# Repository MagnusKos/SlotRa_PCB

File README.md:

# SlotRa_PCB
A rework of [fakeTec_pcb](https://github.com/gargomoma/fakeTec_pcb) project compatible with [Meshtastic](https://meshtastic.org/)®. Based on nRF52840 small boards and cheap LoRa modules identical to RA-62.
This rework rearranges the PCB to become a size of BL-5C battery. It's placed in a custom case project named SlotRa (_to be published_).

__This Readme.md is a modified version of the original one by gargomoma, Big Thanks to them.__

# Pictures
<details><summary>Click to open</summary>

| Just a PCB | A PCB with a batt | A PCB in a slot |
| :------------ | :------------ | :------------ |
| |  |  |

</details>

## Features
- i2c side ports ready to connect an OLED SSD1306 screen.
- Battery sensing: You can use SMD resistors or through-hole.
- 2mm mounting holes.
- Compatible with HT-RA62 / RA-01SH LoRa modules (and probably others with similar footprint).
- The variant & design is based on the DIY
<a href="https://github.com/mrekin/MeshtasticCustomBoards/tree/main/firmware/variants/diy/promicro_diy_m" target="_blank">ProMicro variant</a>.
- As MCU board its used <a href="https://github.com/joric/nrfmicro/wiki/Alternatives#supermini-nrf52840l" target="_blank">ProMicro/SuperMini</a>

# Variants

(aka firmware files)

| Version | Lora Modules | Official Repo link | Unofficial Repo link |
| :------------ | :---------------------------- | :-----------------| :-----------------|
| With TCXO | EByte E22/E220-xxxM-22S/HT-RA62 | <a href="https://github.com/meshtastic/firmware/tree/master/variants/diy/nrf52_promicro_diy_tcxo" target="_blank">Official repo - With TCXO</a> | <a href="https://github.com/mrekin/MeshtasticCustomBoards/tree/main/firmware/variants/diy/promicro_diy_m" target="_blank">With TCXO</a> @mrekin/MeshtasticCustomBoards|
| Without TCXO | EByte E22/E220-xxxMM-22S/RA-01SH | <a href="https://github.com/meshtastic/firmware/tree/master/variants/diy/nrf52_promicro_diy_xtal" target="_blank">Official repo - Without TCXO</a> | <a href="https://github.com/mrekin/MeshtasticCustomBoards/tree/main/firmware/variants/diy/promicro_diy_mm" target="_blank">Without TCXO</a> @mrekin/MeshtasticCustomBoards|

ℹ️If you don't want to build your own image use <a href="https://mrekin.duckdns.org/flasher/" target="_blank">mrekin's flasher</a>

# Bill of materials

| Part | Source | Cost&nbsp;(€) | Note |
| :------------ | :---------------------------- | :-----------------| :-----------------|
| ProMicro (aka NiceNano) | <a href="https://www.aliexpress.com/item/1005006446457448.html" target="_blank">AliExpress</a><br /> <a href="https://www.aliexpress.com/item/1005007738886550.html" target="_blank">AliExpress</a> | 5€ <br /> 2x for 5€ | |
| HT-RA62 | <a href="https://www.aliexpress.com/item/1005005543917617.html" target="_blank">AliExpress</a> | 5€ | You can also use <a href="https://www.aliexpress.com/item/1005002561194884.html">RA-01SH</a> |
| 2x Through Hole Resistors // SMD resistor | <a href="https://www.aliexpress.com/item/1005006044241818.html" target="_blank">AliExpress</a> | 3€ pack<br /> 0.1€/resistor | You can buy a package of multiple values for a few €.<br /> Choose depending on material you already have &/or soldering skills. I'm using 2x 1M ohms |
| OLED SSD1306 i2c (optional) | <a href="https://www.aliexpress.com/item/1005005970901119.html" target="_blank">AliExpress</a> | 1.5€ | No need to solder, just be careful and add some tape in between the boards to avoid a short. |
| Battery connection (optional) | <a href="https://www.aliexpress.com/item/1005002564191148.html" target="_blank">AliExpress</a> | 2€ pack<br /> 0.4€/unit | This is an example. |
| Antenna pigtail (recommended) | <a href="https://www.aliexpress.com/item/4001287491018.html" target="_blank">AliExpress</a> | 2€ | I saw that it underperformed with a cheap black pigtail, after using one of these, it worked fine. |
| PCB |  | 2€ pack of 5<br /> 0.4€/unit | Use your favourite company to get the PCB. |
| 2x Buttons | <a href="https://www.aliexpress.com/item/4001125532910.html" target="_blank">AliExpress</a> | 1.8€ pack<br /> 0.1€/button | You can buy a package of 100 for a few €.<br /> I couldn't find a part code, search for "3*4*2.0 2 Pin Button" |
| [#16](https://github.com/gargomoma/fakeTec_pcb/issues/16) lupusworax's v4<br /> Mosfets SI2312 | <a href="https://www.aliexpress.com/item/1005004676217612.html" target="_blank">AliExpress</a> | 9€ pack of 200<br /> | --- |
| [#16](https://github.com/gargomoma/fakeTec_pcb/issues/16) lupusworax's v4<br /> Resistors | <a href="https://www.aliexpress.com/item/1005002991902748.html" target="_blank">AliExpress</a> | 2.4€ pack of 100<br /> | --- |
|&nbsp;&nbsp;&nbsp;&nbsp;&nbsp;&nbsp;&nbsp;&nbsp;&nbsp;&nbsp;&nbsp;&nbsp;&nbsp;&nbsp;&nbsp;&nbsp;&nbsp;&nbsp;&nbsp;&nbsp;&nbsp;&nbsp;&nbsp;&nbsp;&nbsp;&nbsp;&nbsp;&nbsp;&nbsp;&nbsp;&nbsp;&nbsp;&nbsp;&nbsp;&nbsp;&nbsp;&nbsp;&nbsp;&nbsp;&nbsp;&nbsp;&nbsp;&nbsp;&nbsp;&nbsp;&nbsp;&nbsp;&nbsp;&nbsp;&nbsp;&nbsp;&nbsp;&nbsp;&nbsp;&nbsp;&nbsp;||||
| <strong>Total</strong> || 10€ | |

# Community contributions

| Author | Name | Link |
| :------------ | :------------ | :---------------------------- |
| [lupusworax](https://github.com/gargomoma/fakeTec_pcb/issues/8) | **FakeCAP** | [printables](https://www.printables.com/model/1067553-meshtastic-fakecap-super-slim-nrf52-gps-node) |
| [lupusworax](https://github.com/gargomoma/fakeTec_pcb/issues/8) | **Tamameshi** | [printables](https://www.printables.com/model/1061194-lwc-meshtastic-tamameshi-portable-faketec-node) |
| [lupusworax](https://github.com/gargomoma/fakeTec_pcb/issues/8) | **Meshformer** | [printables](https://www.printables.com/model/1058668-lwc-meshtastic-meshformer-communicator-node) |
| [lupusworax](https://github.com/gargomoma/fakeTec_pcb/issues/8) | **WayPoint** | [printables](https://www.printables.com/model/1104742-meshtastic-waypoint-water-resistant-outdoor-solar) |
| [lupusworax](https://github.com/gargomoma/fakeTec_pcb/issues/8) | **MeshTAK** | [printables](https://www.printables.com/model/1116459-meshtastic-meshtak-tacticool-big-boi-water-resista) |
| [lupusworax](https://github.com/gargomoma/fakeTec_pcb/issues/8) | **SCOUT** | [printables](https://www.printables.com/model/1144370-meshtastic-faketak-scout-ultra-portable-tacticool) |
| [lupusworax](https://github.com/gargomoma/fakeTec_pcb/issues/8) | **F1 Micro** | [printables](https://www.printables.com/model/1123408-meshtastic-faketec-f1-micro-node-nrf52) |
| [mosstrike1](https://cults3d.com/en/users/mosstrike1) | **FakeDeck** | [https://cults3d.com/en/3d-model/various/fakedeck-a-faketek-standalone-meshtastic-device](https://cults3d.com/en/3d-model/various/fakedeck-a-faketek-standalone-meshtastic-device ) |
| [candre23](https://github.com/gargomoma/fakeTec_pcb/issues/5) | **Dummy Model** | [printables](https://www.printables.com/model/1098558-faketec-dummy-model) |
| [candre23](https://github.com/gargomoma/fakeTec_pcb/issues/5) | **p4gr** | [printables](https://www.printables.com/model/1099391-p4gr-a-minimalist-enclosure-for-the-faketec-meshta) |

# Notes

### Bootloader
>Check if the bootloader version is >0.8, update if needed from [here](https://github.com/adafruit/Adafruit_nRF52_Bootloader/releases)
>
>Look for: "update-nice_nano_bootloader-X.X.X_nosd" where X.X.X is the version.
>
>Latest version is: [update-nice_nano_bootloader-0.9.2_nosd.uf2](https://github.com/adafruit/Adafruit_nRF52_Bootloader/releases/download/0.9.2/update-nice_nano_bootloader-0.9.2_nosd.uf2)
>
>To flash all you need to do is to connect the device via USB and double tap RST and GND pins with tweezers. After doing so you should see in your OS a USB storage device named "NICENANO". Copy/move the .uf2 file into the storage device and wait for the reboot.
>
>If you cannot do this, consider the board came without bootloader, keep reading to know how to flash it.

### Charging current
>If you plan to charge the batteries, remember you can increase the charging current by bridging the _boost_ pads at the bottom of the proMicro board.
>You'll find more info on AliExpress listing, and also <a href="https://github.com/joric/nrfmicro/wiki/Alternatives#supermini-nrf52840l" target="_blank">here</a>.
>

### My ProMicro is dead. What can i do?
##### ⚠️ALWAYS TEST THE ProMicros BEFORE SOLDERING!⚠️
>Some sellers sell the ProMicros for very very cheap, but they don't provide bootloader (so you basically got a very smol brick), no problem.

Download the .hex bootloader from [here](https://github.com/adafruit/Adafruit_nRF52_Bootloader/releases) and prepare an ESP32 with the instructions provided [here](https://github.com/atc1441/ESP32_nRF52_SWD).

Latest .hex bootloader is [nice_nano_bootloader-0.9.2_s140_6.1.1.hex](https://github.com/adafruit/Adafruit_nRF52_Bootloader/releases/download/0.9.2/nice_nano_bootloader-0.9.2_s140_6.1.1.hex).

Once you got the ESP32 board ready, solder `CLK`,`DIO`,`GND`,`VDD` (or the `3v`) to the corresponding pins on the ESP32. (The ProMicro pins are on the back of the board.)

Then:
 1. Power the ESP32 on, on your browser open swd.local (or the IP assigned)
 2. Click Init SWD (if the "Status" shows not okay, check the wiring)
 3. Erase nRF -> Ok: Everything erased (if nRF info mentions locked, erase & reset)
 4. Flash Uploaded File -> Select file (the .hex bootloader), offset = 0
 5. Flash uploaded File; Wait for the upload to complete.
 6. 🧟‍♀️IT'S ALIVEEEE🧟‍♀️

# ♥Thanks♥
Thanks to all the folks in the [Discord nRF52 chat](https://discord.com/channels/867578229534359593/1194757507013427250) for the support on designing this board ♥
And thank you to the people contributing with their own designs (see Community contributions).

# About Meshtastic
[Meshtastic](https://meshtastic.org/)® is a registered trademark of Meshtastic LLC. Meshtastic software components are released under various licenses, see github for details.

# Disclaimer
No warranty is provided.
You use it at your own risk and take the responsibility upon yourself.

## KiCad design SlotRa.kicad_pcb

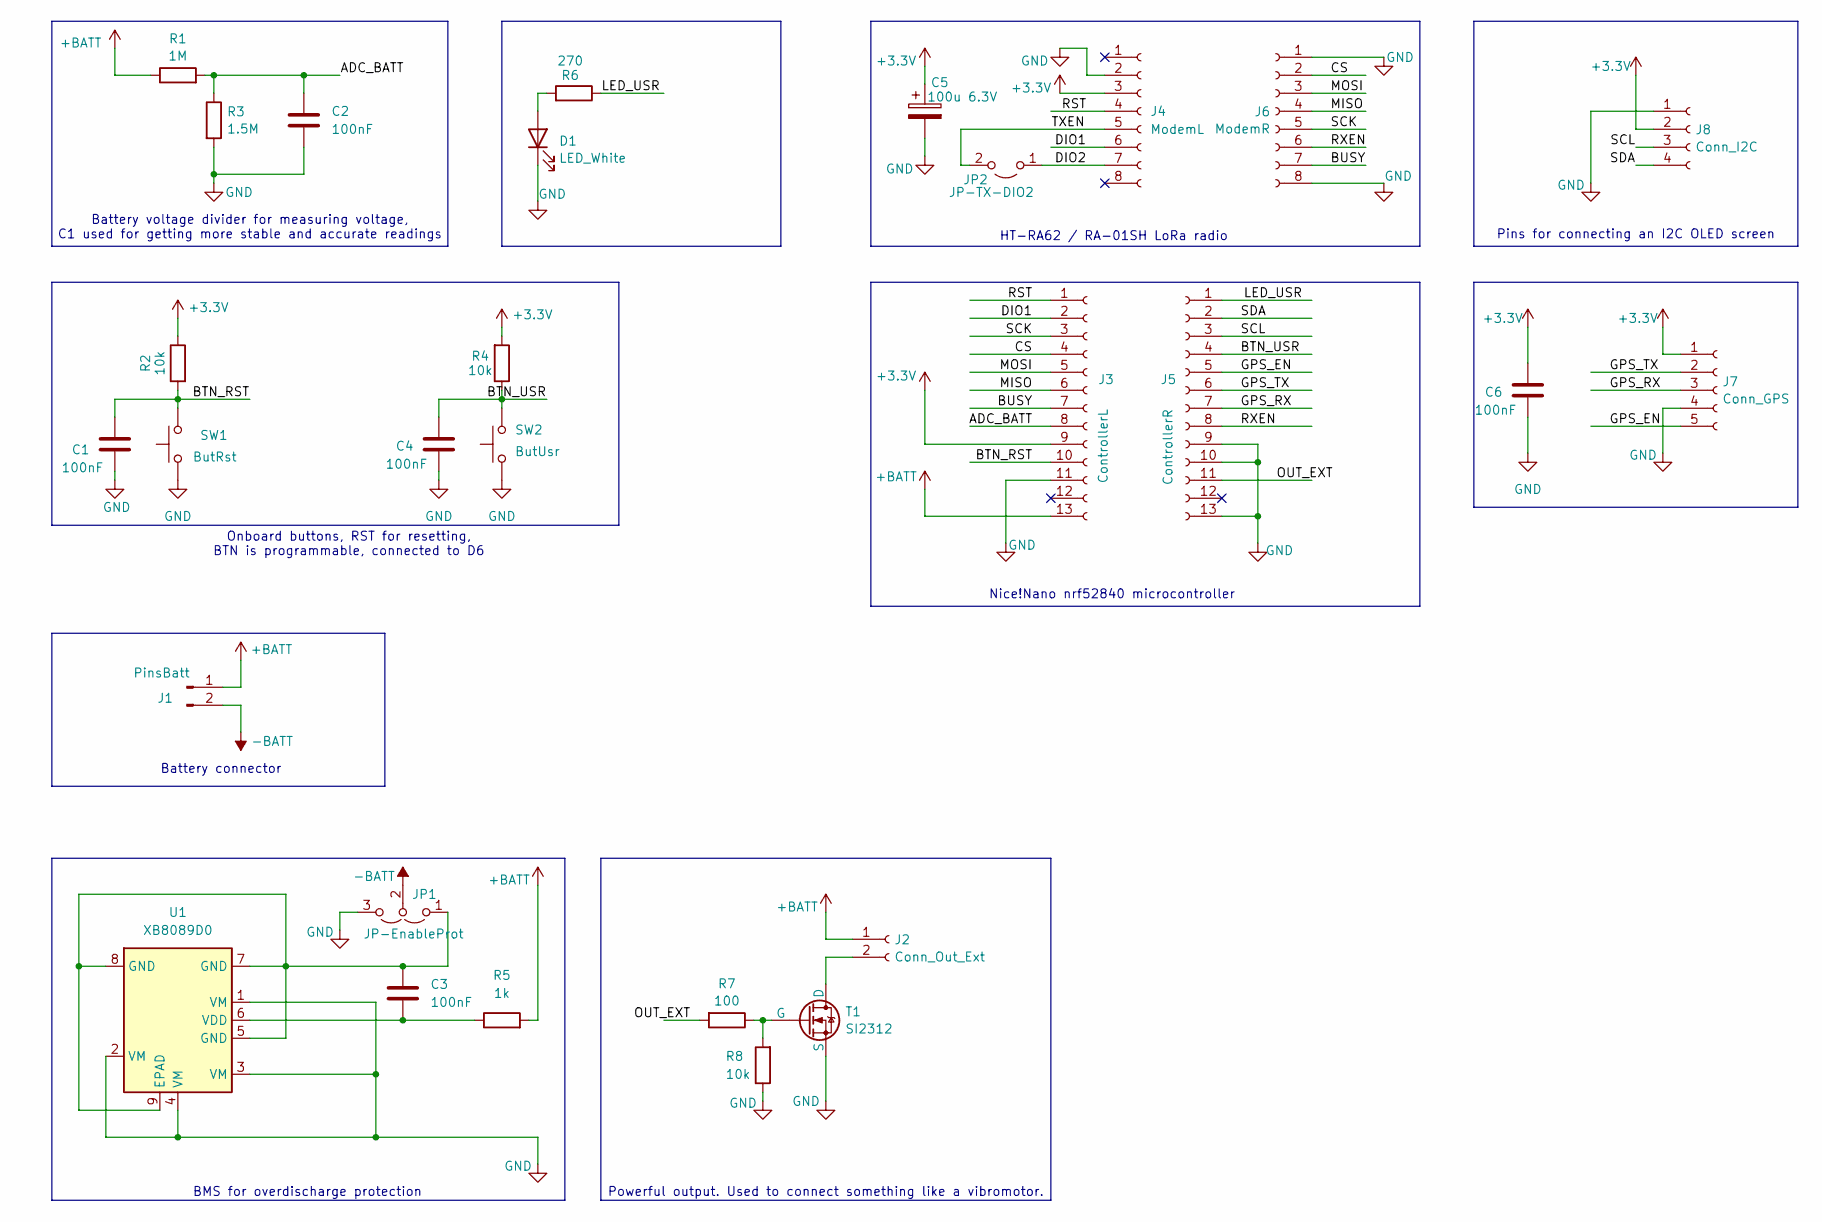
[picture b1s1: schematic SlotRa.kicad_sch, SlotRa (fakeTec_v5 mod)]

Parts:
C1, C2, C3, C4, C6: 100nF; C_0805_2012Metric_Pad1.18x1.45mm_HandSolder
C5: 100u 6.3V; CP_EIA-7343-31_Kemet-D
D1: LED_White; LED_D3.0mm_Horizontal_O6.35mm_Z10.0mm
J1: PinsBatt; PinHeader_1x02_P2.54mm_Vertical
J2: Conn_Out_Ext; PinHeader_1x02_P2.54mm_Vertical
J3: ControllerL; SMD_Pad_Row_P2.54_13x1
J4: ModemL; SMD_Pad_Row_P2.00_8x1_longer
J5: ControllerR; SMD_Pad_Row_P2.54_13x1
J6: ModemR; SMD_Pad_Row_P2.00_8x1
J7: Conn_GPS; PinHeader_1x05_P2.00mm_Vertical
J8: Conn_I2C; PinHeader_1x04_P2.54mm_Vertical
JP1: JP-EnableProt; SolderJumper-3_P1.3mm_Open_RoundedPad1.0x1.5mm
JP2: JP-TX-DIO2; SolderJumper-2_P1.3mm_Open_RoundedPad1.0x1.5mm
R1: 1M; R_0805_2012Metric_Pad1.20x1.40mm_HandSolder
R2, R4, R8: 10k; R_0805_2012Metric_Pad1.20x1.40mm_HandSolder
R3: 1.5M; R_0805_2012Metric_Pad1.20x1.40mm_HandSolder
R5: 1k; R_0805_2012Metric_Pad1.20x1.40mm_HandSolder
R6: 270; R_0805_2012Metric_Pad1.20x1.40mm_HandSolder
R7: 100; R_0805_2012Metric_Pad1.20x1.40mm_HandSolder
SW1: ButRst; KLS7-TS6335
SW2: ButUsr; PinHeader_1x02_P2.54mm_Vertical
T1: SI2312; TSOT-23_HandSoldering_Updated
U1: XB8089D0; SOIC-8-1EP_3.9x4.9mm_P1.27mm_EP2.41x3.3mm

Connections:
+3.3V: C5.1, C6.2, J3.9, J4.3, J7.1, J8.2, R2.1, R4.2
+BATT: J1.1, J2.1, J3.13, R1.1, R5.2
-BATT: J1.2, JP1.2 (C)
/ADC_BATT: C2.1, J3.8, R1.2, R3.1
/BTN_RST: C1.1, J3.10, R2.2, SW1.2
/BTN_USR: C4.2, J5.4, R4.1, SW2.2
/BUSY: J3.7, J6.7
/CS: J3.4, J6.2
/DIO1: J3.2, J4.6
/DIO2: J4.7, JP2.1 (A)
/GPS_EN: J5.5, J7.5
/GPS_RX: J5.7, J7.3
/GPS_TX: J5.6, J7.2
/LED_USR: J5.1, R6.1
/MISO: J3.6, J6.4
/MOSI: J3.5, J6.3
/OUT_EXT: J5.11, R7.2
/RST: J3.1, J4.4
/RXEN: J5.8, J6.6
/SCK: J3.3, J6.5
/SCL: J5.3, J8.3
/SDA: J5.2, J8.4
/TXEN: J4.5, JP2.2 (B)
GND: C1.2, C2.2, C4.1, C5.2, C6.1, D1.1 (K), J3.11, J4.2, J5.9, J5.10, J5.13, J6.1, J6.8, J7.4, J8.1, JP1.3 (B), R3.2, R8.1, SW1.1, SW2.1, T1.3 (S), U1.1 (VM), U1.2 (VM), U1.3 (VM), U1.4 (VM)
unnamed: D1.2 (A), R6.2
unnamed: J2.2, T1.1 (D)
unnamed: C3.1, JP1.1 (A), U1.5 (GND), U1.7 (GND), U1.8 (GND), U1.9 (EPAD)
unnamed: R7.1, R8.2, T1.2 (G)
unnamed: C3.2, R5.1, U1.6 (VDD)

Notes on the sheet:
Nice!Nano nrf52840 microcontroller
Powerful output. Used to connect something like a vibromotor.
BMS for overdischarge protection
Battery voltage divider for measuring voltage, C1 used for getting more stable and accurate readings
HT-RA62 / RA-01SH LoRa radio
Onboard buttons, RST for resetting, BTN is programmable, connected to D6
Battery connector
Pins for connecting an I2C OLED screen

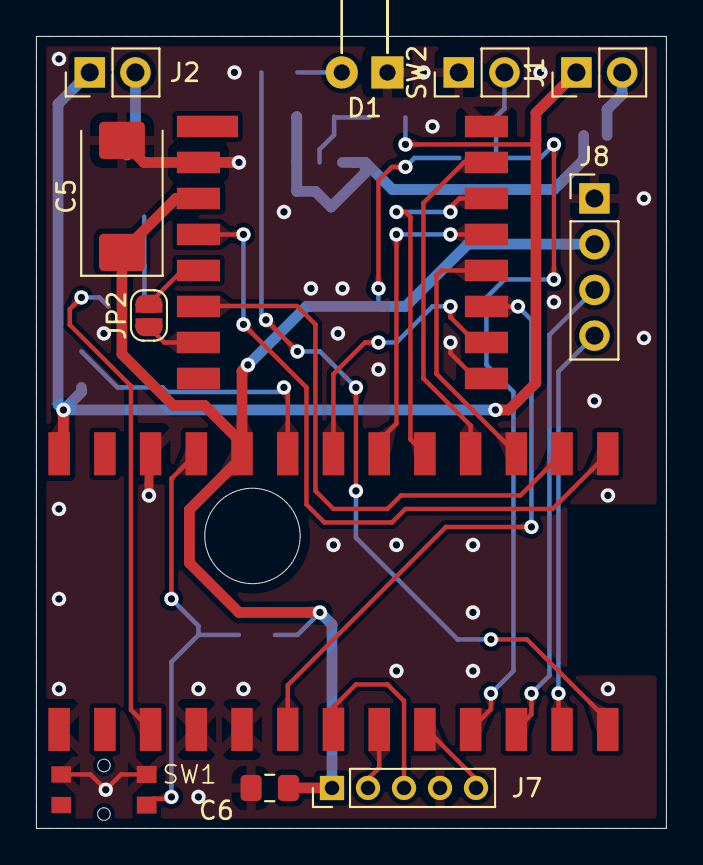
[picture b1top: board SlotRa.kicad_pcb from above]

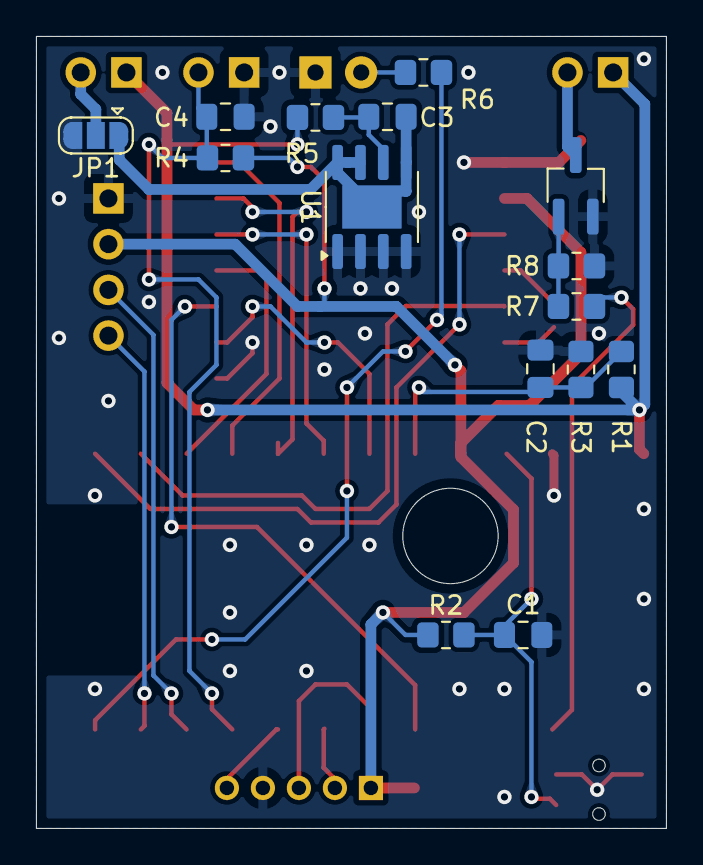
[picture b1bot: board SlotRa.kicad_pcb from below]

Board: 2 copper layers, 35.0 x 44.0 mm, 29 parts (15 on the bottom side), 29 nets.

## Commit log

2025-05-23 Structure cleansing
    Unpacked archive in the root: archived files are the project files.
    Excluded gerbers: these files are generated ones, they'll become Released ones.
    Deleted pics: new images are coming.
2025-05-23 Update README.md
    Just a small fork-oriented adjustments. This is not a final version.
2025-05-24 Project renaming, cleansing and small additions
    Renamed kicad files.
    Performed some beautifications in the schematics for a better readability.
    Added gate resistors.
    Added arbitrary led for notifications.
    Added an e-capacitor for the modem powering filtering and stability improvements.
2025-05-24 Honey, I Shrunk The Footprints
    1206 caps and ress are 0805 now. They're cheaper, have suitable voltage and power ratings, and are still easy to solder.
    Also the author have a bunch of them, but not the 1206 ones...
2025-05-24 TXEN - DIO2 jumper
    It is unknown why these modem pads are hard-connected. If one needs this behavior - there is a jumper for it now.
2025-05-25 Buses renaming, power reconnection
    I can't understand why there are labeled connections with creepy names that doubles already existing buses. So, say goodbye to that labels and say hello to clean and logical named bus symbols.
    Also renamed Batt-Percent. Looks like some kind of expression, but actually it is indeed a connection to voltage-measuring line. I prefer ADC_BATT for that purpose.
    Renamed jumpers' labels.
    Deleted one of the battery connectors: no need to use redundancy in this fork.
2025-05-25 GPS port and uC-PCB schematics
    And now the PCB's pin-headers become readable in the schematics.
    GPS's pins are separated, I dunno why they used 4-pin pads with attached user button, but no power buses at all. Now there are 5-pin pads with mandatory power and data lines and an optional enable si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
    Removed the first power mosfet that also could regulate GPS's power. Let's make it something external. What if the GPS unit already has EN signal?
2025-05-27 Transistors purging and more adjustments
    And now there is only one power MOSFET. One can connect it to a vibromotor, for example. Also it uses pin-header with 2 pins: 1 connected to a battery line and one - to the MOSFET.
    There are also some minor schematic and symbols adjustments.
2025-05-28 Finally, The PCB
    Small fixes in the schematics.
    Recreated the PCB. A toucght one, there were too many wrong decisions that led to a non-upgradability of the project without the Power Of Some Mother And The Sledgehammer.
2025-05-28 Custom footprints library
    This project initially used a lot of custom-made (or ported) footprints, that breaks by the easiest blow of the wind. So, here is a library. With all the things, that are used in the project.
2025-05-28 Eye candy for the PCB
    I like rounded tracks. No more to say.
    So here are static project files with a rounded tracks. They are not connected to the schematics (kinda) and to the original PCB, so use 'em and be warned about a lag.
2025-05-28 Quick Fix: MOSFET line
    Just a quick fix: T1 Drain circuit was too thin. It's in the Power family now, so the line is thick.
2025-07-17 A bunch of photos
    Added some crappy photos of the PCB.
    Integrated photos in Readme.md.
